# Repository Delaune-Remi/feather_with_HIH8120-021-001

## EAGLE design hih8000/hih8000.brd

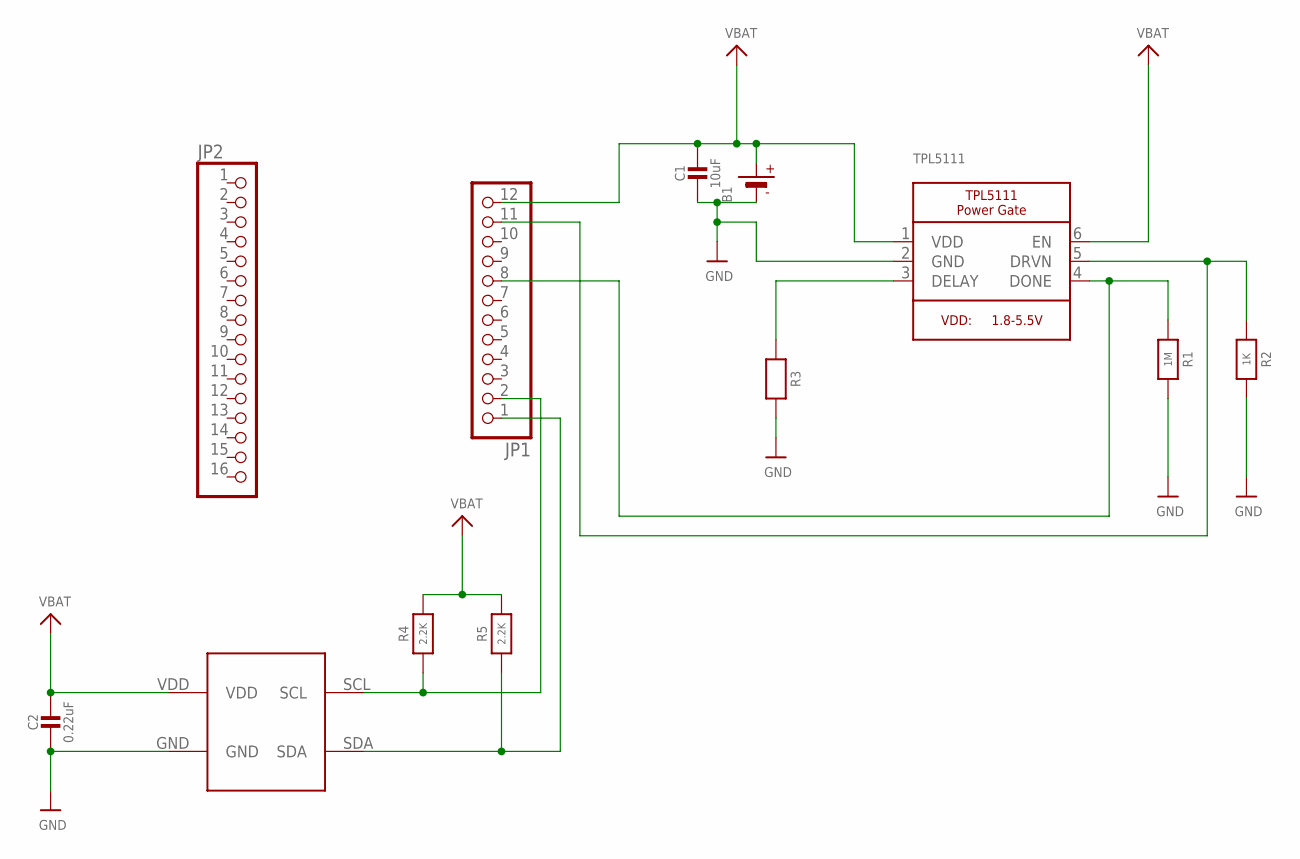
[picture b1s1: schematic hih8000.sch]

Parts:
B1: BATTERY; JSTPH2
C1: 10uF; 0805-NO
C2: 0.22uF; 0805-NO
JP1: HEADER-1X12; 1X12_ROUND
JP2: HEADER-1X16ROUND; 1X16_ROUND
R1: 1M; 0805-NO
R2: 1K; 0805-NO
R3: RESISTOR0805_NOOUTLINE; 0805-NO
R4, R5: 2.2K; 0805-NO
TPL5111: TPL5111; SOT23-6
U$7: HIH8000_DEV; HIH8000

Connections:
GND: B1.1 (-), C1.2, C2.2, R1.2, R2.2, R3.2, TPL5111.2 (GND), U$7.GND
unnamed: JP1.11, R2.1, TPL5111.5 (DRVN)
unnamed: JP1.8, R1.1, TPL5111.4 (DONE)
unnamed: R3.1, TPL5111.3 (DELAY)
unnamed: JP1.2, R4.1, U$7.SCL
unnamed: JP1.1, R5.1, U$7.SDA
VBAT: B1.2 (+), C1.1, C2.1, JP1.12, R4.2, R5.2, TPL5111.1 (VDD), TPL5111.6 (EN), U$7.VDD

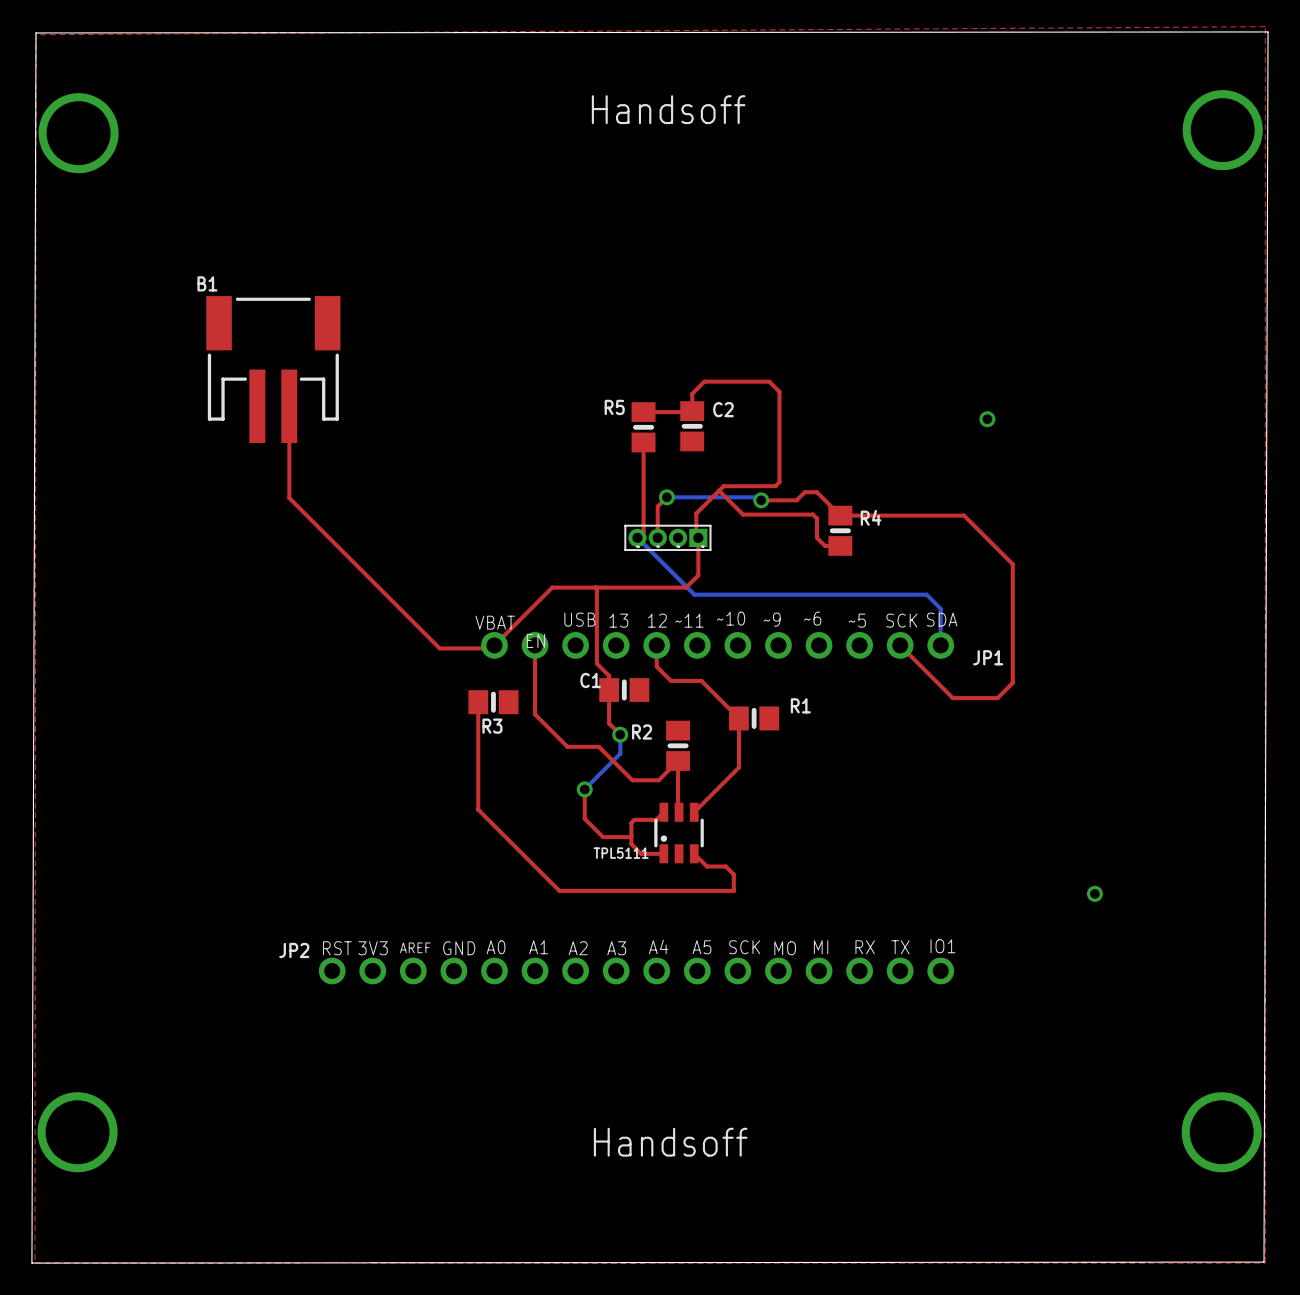
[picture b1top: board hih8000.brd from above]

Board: 2 copper layers, 77.4 x 77.1 mm, 12 parts (0 on the bottom side), 7 nets.

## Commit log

2017-12-26 sensor code
2017-12-26 eagle pcb design
2017-12-26 pcb design folder name change
2017-12-26 Remove duplicate directories
